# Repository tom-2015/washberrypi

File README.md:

# WashberryPi
The main controller board of our washing machine was broken so I decided to do something stupid: create a new controller board with a Raspberry Pi on it!
It turned out not so easy as thought, especially starting centrifuge without having unbalance making the machine to start walking proved a challenge.
After a few months testing and designing new PCB it was finally working again. It's not yet fully completed but if anyone else ever wants to do something this crazy I decided to put everything open source on github.

# Requirements
It's designed for a Samsung co bubble with DC motor but with some adjustments in software and PCB it will probably work with other machines that have a DC motor.
You'll need some skills for PCB design in Eagle, programming Raspberry Pi (Visual Basic .NET) and microcontrollers (Microchip PIC) in C.

# Contens
The repository contains 4 projects:
* Washmachine.sln: the main Visual Studio VB .NET project with software that runs on the Raspberry. This project is the main program of the washing machine. It controls all the components and provides a web interface.
* eagle directory: contains the Eagle files and Gerber files for the PCB that holds the Raspberry Pi Zero W, PIC microcontroller, relays and motor control components.
* pic directory: contains washing_machine.__c which is a Source Boost project containing C-code for the microcontroller that drives the TRIAC for motor.
* www directory: this is the web interface main directory.

# TIPS
Some tips if you want to make your washing machine Raspberry Pi controlled:
* be careful when applying power to the motor, I accidently applied power too fast resulting in a broken bearing! When testing the motor circuit add some resistors in series with the motor.
* If I need to redo the project I would consider using PWM with an IGBT or MOSFET to drive the motor and not using the original Samsung design with a TRIAC. This is because I think it's easier using PWM which in theory could be connected directly to the Pi instead of having a different microcontroller for it.
* Use a Raspberry Pi (2,3,4) with quad core instead of the single core Raspberry Pi Zero W. I needed to use an accelerometer to capture the drum vibrations and this required a thread to read 400 samples a second over I²C. This single core is often interrupted doing other stuff making the accelerometer buffer overflow.

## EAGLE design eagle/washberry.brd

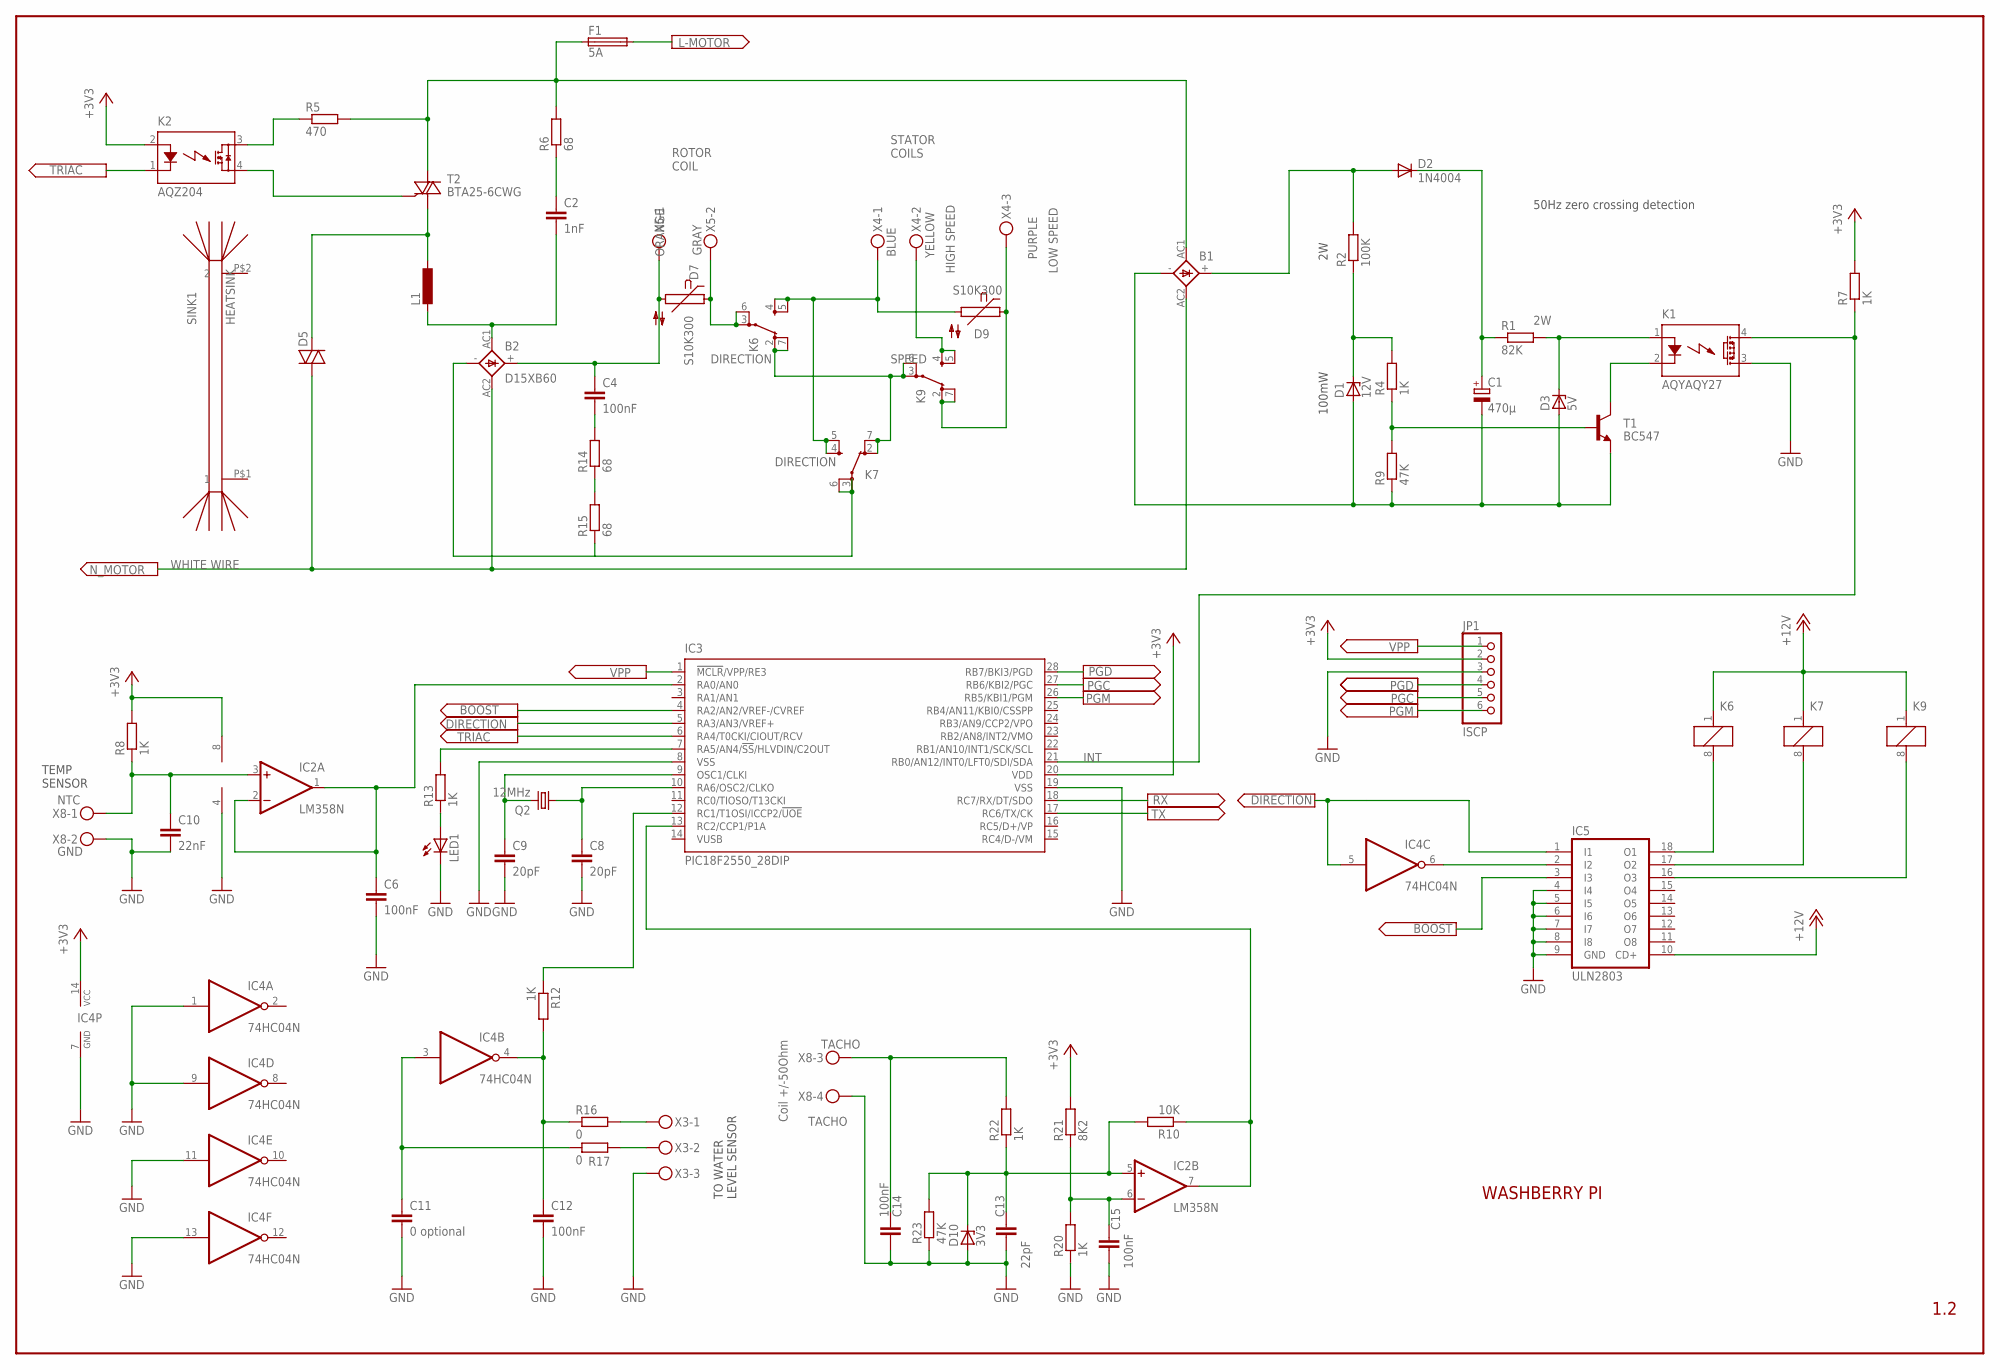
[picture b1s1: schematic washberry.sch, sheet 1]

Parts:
B1: 2KBB
B2: D15XB60; 5S
C1: 470µ; E5-13
C2: 1nF; C150-054X183
C4: 100nF; C150-054X183
C6, C12, C14, C15: 100nF; C025-024X044
C8, C9: 20pF; C025-024X044
C10: 22nF; C025-024X044
C11: 0 optional; C025-024X044
C13: 22pF; C025-024X044
D1: 12V; DO34Z7
D2: 1N4004; DO41-10
D3: 5V; DO34Z7
D5: DIAC-DO35-10; DO35-10
D7, D9: S10K300
D10: 3V3; DO34Z7
F1: 5A; GSH15
IC2: LM358N; DIL08
IC3: PIC18F2550_28DIP; DIL28-3
IC4: 74HC04N; DIL14
IC5: ULN2803; DIL18
JP1: ISCP; 1X06
K1: AQYAQY27; AQY27
K2: AQZ204; AQZ-SIL04
K6, K7, K9: FTR-K1C
L1: L-EUTJ5-U1; TJ5-U1
LED1: LEDCHIPLED_0805; CHIPLED_0805
Q2: 12MHz; HC49/S
R1: 82K; 0617/17
R2: 100K; 0617/17
R4, R7, R8, R12, R20, R22: 1K; 0411V
R5: 470; P0613/15
R6: 68; P0613/15
R9, R23: 47K; 0411V
R10: 10K; 0411V
R13: 1K; R0805
R14, R15: 68; 0617/17
R16, R17: 0; 0411V
R21: 8K2; 0411V
SINK1: HEATSINK; W_HEATSINK
T1: BC547; TO92
T2: BTA25-6CWG; TO220BV
X3, X4: MKDSN1,5/3-5,08
X5: MKDSN1,5/2-5,08
X8: MKDSN1,5/9-5,08

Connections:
+3V3: IC2.8 (V+), IC3.20 (VDD), IC4.14 (VCC), JP1.2, K2.2 (A), R7.2, R8.2, R21.2; also elsewhere on the board
+12V: IC5.10 (CD+), K6.1, K7.1, K9.1; also elsewhere on the board
BOOST: IC3.4 (RA2/AN2/VREF-/CVREF), IC5.3 (I3)
DIRECTION: IC3.5 (RA3/AN3/VREF+), IC4.5 (I), IC5.1 (I1)
GND: C6.2, C8.2, C9.2, C10.2, C11.2, C12.2, C13.2, C14.2, C15.2, D10.A, IC2.4 (V-), IC3.8 (VSS), IC3.19 (VSS), IC4.1 (I), IC4.7 (GND), IC4.9 (I), IC4.11 (I), IC4.13 (I), IC5.4 (I4), IC5.5 (I5), IC5.6 (I6), IC5.7 (I7), IC5.8 (I8), IC5.9 (GND), JP1.3, K1.3 (DS2), LED1.C, R20.1, R23.1, X3.3, X8.2, X8.4; also elsewhere on the board
INT: IC3.21 (RB0/AN12/INT0/LFT0/SDI/SDA), K1.4 (DS1), R7.1
L-MOTOR: F1.2; also elsewhere on the board
unnamed: K1.2 (K), T1.3 (C)
unnamed: B1.-, C1.-, D1.A, D3.A, R9.1, T1.1 (E)
unnamed: C1.+, D2.C, R1.1
unnamed: D3.C, K1.1 (A), R1.2
unnamed: IC3.7 (RA5/AN4/!SS!/HLVDIN/C2OUT), R13.2
unnamed: LED1.A, R13.1
unnamed: D1.C, R2.1, R4.2
unnamed: R4.1, R9.2, T1.2 (B)
unnamed: B1.+, D2.A, R2.2
unnamed: K2.4 (DS2), T2.G
unnamed: K2.3 (DS1), R5.1
unnamed: IC2.7 (OUT), IC3.13 (RC2/CCP1/P1A), R10.1
unnamed: B2.-, K7.3 (PA), K7.6 (PB), R15.1
unnamed: C2.1, R6.1
unnamed: B2.AC1, C2.2, L1.2
unnamed: C6.1, IC2.1 (OUT), IC2.2 (-IN), IC3.2 (RA0/AN0)
unnamed: K9.4 (SA), K9.5 (SB), X4.2
unnamed: D9.1, K9.2 (OA), K9.7 (OB), X4.3
unnamed: D5.C (2), L1.1, T2.T1 (A1)
unnamed: B2.+, C4.1, D7.2, X5.1
unnamed: C9.1, IC3.9 (OSC1/CLKI), Q2.2
unnamed: C8.1, IC3.10 (RA6/OSC2/CLKO), Q2.1
unnamed: IC3.12 (RC1/T1OSI/ICCP2/!UOE), R12.1
unnamed: C11.1, IC4.3 (I), R17.1
unnamed: C12.1, IC4.4 (O), R12.2, R16.1
unnamed: R14.1, R15.2
unnamed: C4.2, R14.2
unnamed: K6.2 (OA), K6.7 (OB), K7.2 (OA), K7.7 (OB), K9.3 (PA), K9.6 (PB)
unnamed: D9.2, K6.4 (SA), K6.5 (SB), K7.4 (SA), K7.5 (SB), X4.1
unnamed: D7.1, K6.3 (PA), K6.6 (PB), X5.2
unnamed: IC5.18 (O1), K6.8 (2)
unnamed: R16.2, X3.1
unnamed: R17.2, X3.2
unnamed: C15.1, IC2.6 (-IN), R20.2, R21.1
unnamed: C13.1, D10.C, IC2.5 (+IN), R10.2, R22.1, R23.2
unnamed: IC4.6 (O), IC5.2 (I2)
unnamed: IC5.17 (O2), K7.8 (2)
unnamed: IC5.16 (O3), K9.8 (2)
NTC: C10.1, IC2.3 (+IN), R8.1, X8.1
N_MOTOR: B1.AC2, B2.AC2, D5.A (1); also elsewhere on the board
PGC: IC3.27 (RB6/KBI2/PGC), JP1.5
PGD: IC3.28 (RB7/BKI3/PGD), JP1.4
PGM: IC3.26 (RB5/KBI1/PGM), JP1.6
RX: IC3.18 (RC7/RX/DT/SDO); also elsewhere on the board
SUPPLY_MOTOR: B1.AC1, F1.1, R5.2, R6.2, T2.T2 (A2)
TACHO: C14.1, R22.2, X8.3
TRIAC: IC3.6 (RA4/T0CKI/CIOUT/RCV), K2.1 (K)
TX: IC3.17 (RC6/TX/CK); also elsewhere on the board
VPP: IC3.1 (!MCLR!/VPP/RE3), JP1.1

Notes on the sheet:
100mW
TEMP SENSOR
WASHBERRY PI
1.2
ROTOR COIL
STATOR COILS
LOW SPEED
HIGH SPEED
DIRECTION
SPEED
50Hz zero crossing detection
WHITE WIRE
ORANGE
GRAY
BLUE
YELLOW
PURPLE
Coil +/-50Ohm
TO WATER LEVEL SENSOR

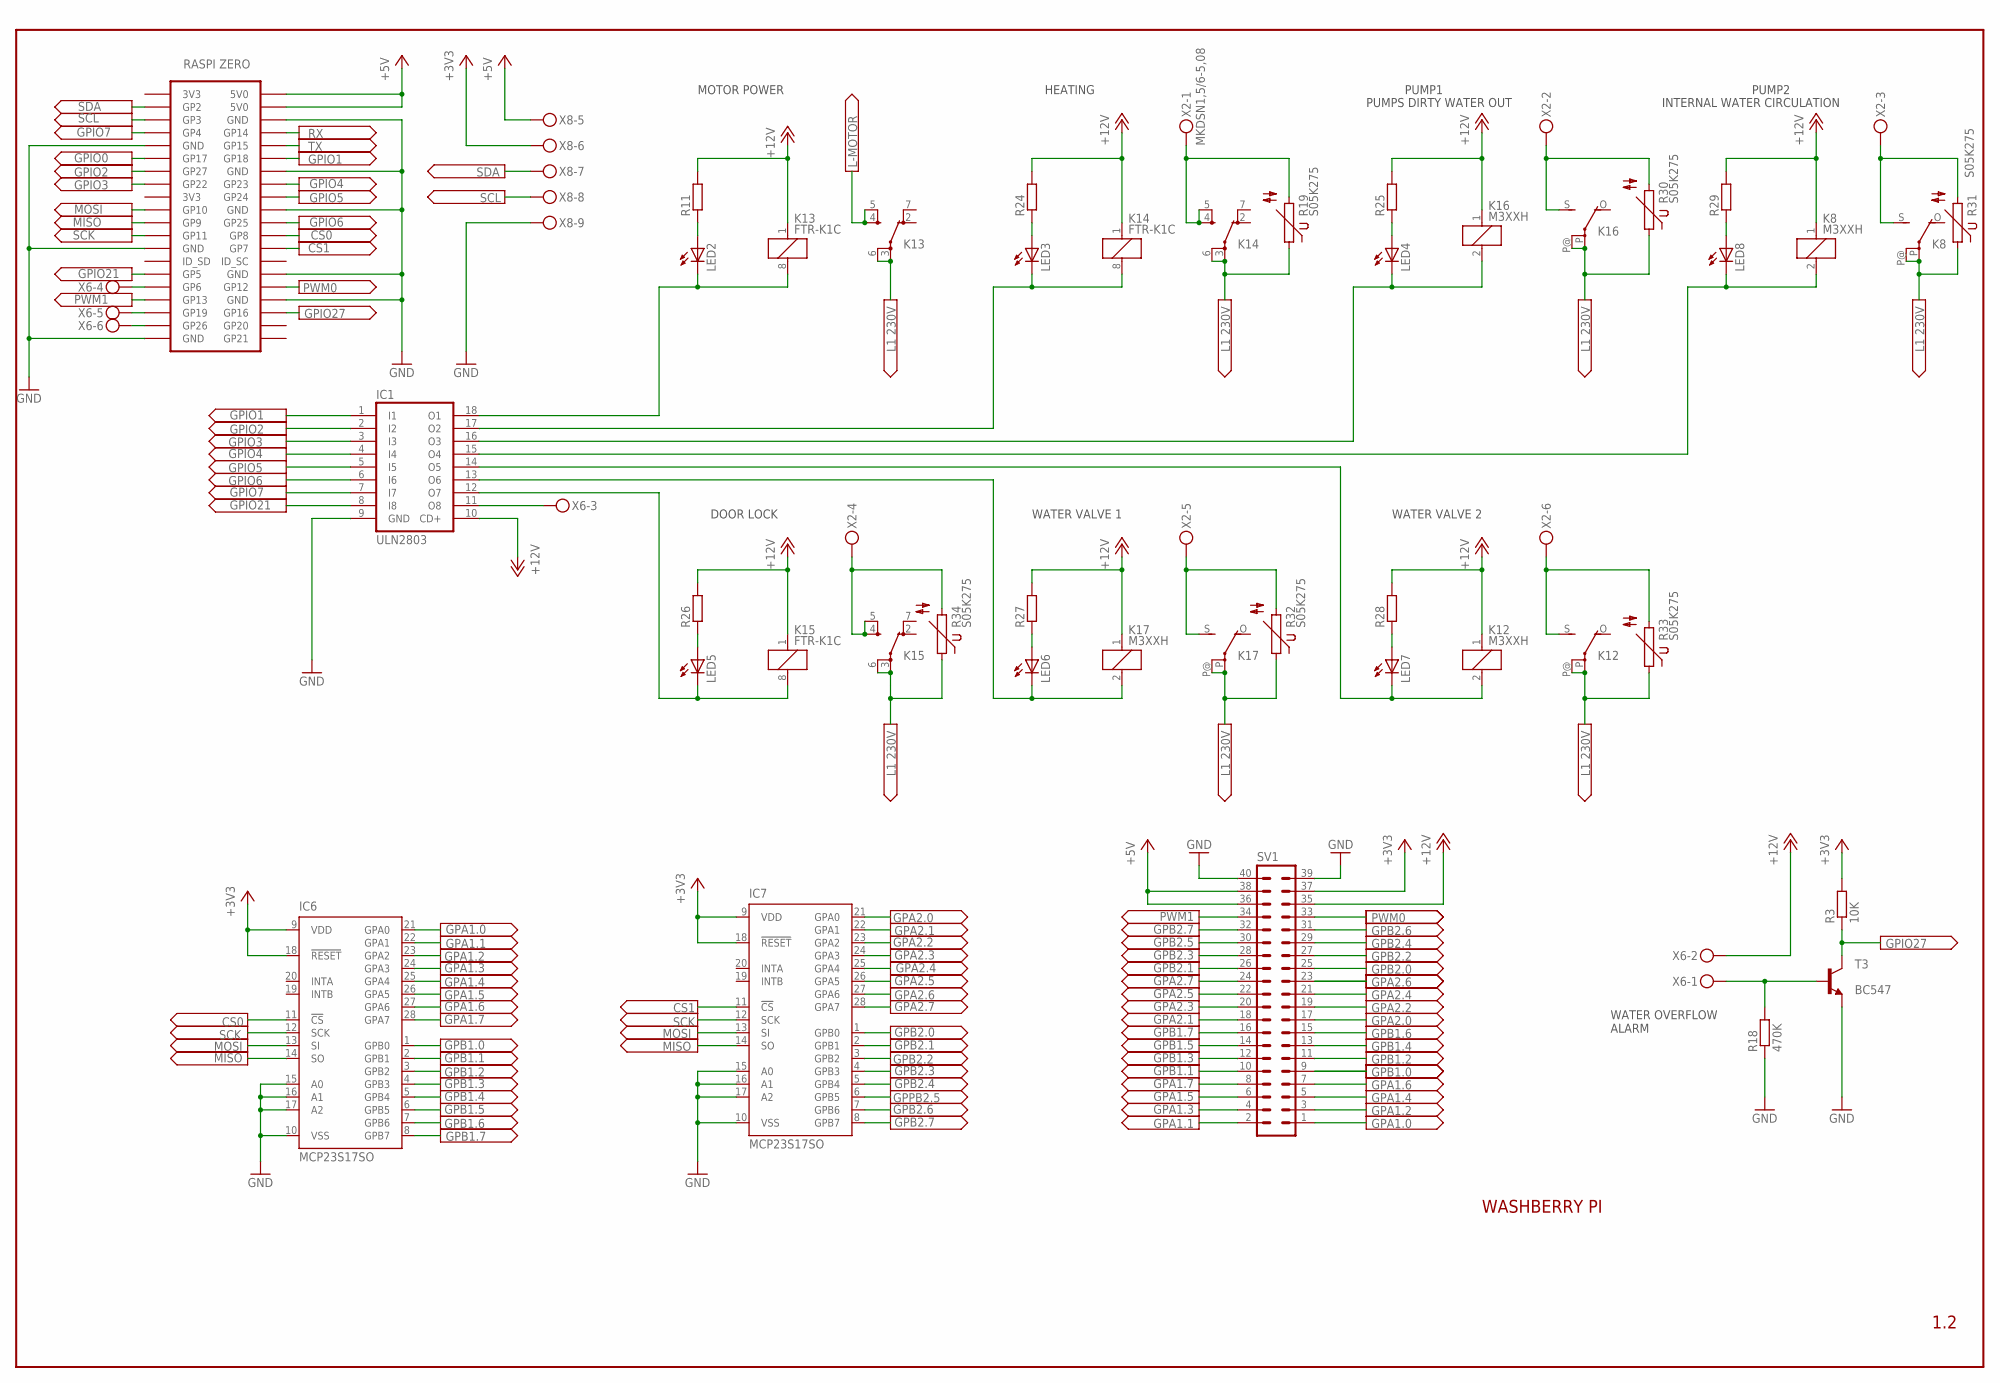
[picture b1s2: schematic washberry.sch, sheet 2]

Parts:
IC1: ULN2803; DIL18
IC6, IC7: MCP23S17SO; SO28W
K8, K12, K16, K17: M3XXH
K13, K14, K15: FTR-K1C
LED2, LED3, LED4, LED5, LED6, LED7, LED8: LEDSML0805; SML0805
R3: 10K; 0207/2V
R11, R24, R25, R26, R27, R28, R29: R-EU_R0805; R0805
R18: 470K; 0207/2V
R19, R30, R31, R32, R33, R34: S05K275
SV1: ML40
T3: BC547; TO92
U$3: ZERO; ZERO_NO_DIMENSION
X2, X6: MKDSN1,5/6-5,08
X8: MKDSN1,5/9-5,08

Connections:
+3V3: IC6.9 (VDD), IC6.18 (!RESET), IC7.9 (VDD), IC7.18 (!RESET), R3.2, SV1.37, X8.6; also elsewhere on the board
+5V: SV1.36, SV1.38, U$3.2 (5V0), U$3.4 (5V0), X8.5; also elsewhere on the board
+12V: IC1.10 (CD+), K8.1, K12.1, K13.1, K14.1, K15.1, K16.1, K17.1, R11.2, R24.2, R25.2, R26.2, R27.2, R28.2, R29.2, SV1.35, X6.2; also elsewhere on the board
CS0: IC6.11 (!CS), U$3.24 (GP8)
CS1: IC7.11 (!CS), U$3.26 (GP7)
GND: IC1.9 (GND), IC6.10 (VSS), IC6.15 (A0), IC6.16 (A1), IC6.17 (A2), IC7.10 (VSS), IC7.15 (A0), IC7.16 (A1), IC7.17 (A2), R18.1, SV1.39, SV1.40, T3.1 (E), U$3.6 (GND), U$3.9 (GND), U$3.14 (GND), U$3.20 (GND), U$3.25 (GND), U$3.30 (GND), U$3.34 (GND), U$3.39 (GND), X8.9; also elsewhere on the board
GPA1.0: IC6.21 (GPA0), SV1.1
GPA1.1: IC6.22 (GPA1), SV1.2
GPA1.2: IC6.23 (GPA2), SV1.3
GPA1.3: IC6.24 (GPA3), SV1.4
GPA1.4: IC6.25 (GPA4), SV1.5
GPA1.5: IC6.26 (GPA5), SV1.6
GPA1.6: IC6.27 (GPA6), SV1.7
GPA1.7: IC6.28 (GPA7), SV1.8
GPA2.0: IC7.21 (GPA0), SV1.17
GPA2.1: IC7.22 (GPA1), SV1.18
GPA2.2: IC7.23 (GPA2), SV1.19
GPA2.3: IC7.24 (GPA3), SV1.20
GPA2.4: IC7.25 (GPA4), SV1.21
GPA2.5: IC7.26 (GPA5), SV1.22
GPA2.6: IC7.27 (GPA6), SV1.23
GPA2.7: IC7.28 (GPA7), SV1.24
GPB1.0: IC6.1 (GPB0), SV1.9
GPB1.1: IC6.2 (GPB1), SV1.10
GPB1.2: IC6.3 (GPB2), SV1.11
GPB1.3: IC6.4 (GPB3), SV1.12
GPB1.4: IC6.5 (GPB4), SV1.13
GPB1.5: IC6.6 (GPB5), SV1.14
GPB1.6: IC6.7 (GPB6), SV1.15
GPB1.7: IC6.8 (GPB7), SV1.16
GPB2.0: IC7.1 (GPB0), SV1.25
GPB2.1: IC7.2 (GPB1), SV1.26
GPB2.2: IC7.3 (GPB2), SV1.27
GPB2.3: IC7.4 (GPB3), SV1.28
GPB2.4: IC7.5 (GPB4), SV1.29
GPB2.5: SV1.30
GPB2.6: IC7.7 (GPB6), SV1.31
GPB2.7: IC7.8 (GPB7), SV1.32
GPIO0: U$3.11 (GP17)
GPIO1: IC1.1 (I1), U$3.12 (GP18)
GPIO2: IC1.2 (I2), U$3.13 (GP27)
GPIO3: IC1.3 (I3), U$3.15 (GP22)
GPIO4: IC1.4 (I4), U$3.16 (GP23)
GPIO5: IC1.5 (I5), U$3.18 (GP24)
GPIO6: IC1.6 (I6), U$3.22 (GP25)
GPIO7: IC1.7 (I7), U$3.7 (GP4)
GPIO21: IC1.8 (I8), U$3.29 (GP5)
GPIO27: R3.1, T3.3 (C), U$3.36 (GP16)
GPPB2.5: IC7.6 (GPB5)
L: K8.P, K8.P@, K12.P, K12.P@, K13.3 (PA), K13.6 (PB), K14.3 (PA), K14.6 (PB), K15.3 (PA), K15.6 (PB), K16.P, K16.P@, K17.P, K17.P@, R19.1, R30.1, R31.1, R32.1, R33.1, R34.1; also elsewhere on the board
L-MOTOR: K13.4 (SA), K13.5 (SB); also elsewhere on the board
MISO: IC6.14 (SO), IC7.14 (SO), U$3.21 (GP9)
MOSI: IC6.13 (SI), IC7.13 (SI), U$3.19 (GP10)
unnamed: IC1.11 (O8), X6.3
unnamed: R18.2, T3.2 (B), X6.1
unnamed: IC1.18 (O1), K13.8 (2), LED2.C
unnamed: LED2.A, R11.1
unnamed: IC1.17 (O2), K14.8 (2), LED3.C
unnamed: LED3.A, R24.1
unnamed: IC1.16 (O3), K16.2, LED4.C
unnamed: U$3.31 (GP6), X6.4
unnamed: U$3.35 (GP19), X6.5
unnamed: LED4.A, R25.1
unnamed: LED5.A, R26.1
unnamed: IC1.13 (O6), K17.2, LED6.C
unnamed: LED6.A, R27.1
unnamed: IC1.14 (O5), K12.2, LED7.C
unnamed: LED7.A, R28.1
unnamed: IC1.15 (O4), K8.2, LED8.C
unnamed: LED8.A, R29.1
unnamed: IC1.12 (O7), K15.8 (2), LED5.C
unnamed: U$3.37 (GP26), X6.6
unnamed: K14.4 (SA), K14.5 (SB), R19.2, X2.1
unnamed: K16.S, R30.2, X2.2
unnamed: K8.S, R31.2, X2.3
unnamed: K12.S, R33.2, X2.6
unnamed: K17.S, R32.2, X2.5
unnamed: K15.4 (SA), K15.5 (SB), R34.2, X2.4
PWM0: SV1.33, U$3.32 (GP12)
PWM1: SV1.34, U$3.33 (GP13)
RX: U$3.8 (GP14); also elsewhere on the board
SCK: IC6.12 (SCK), IC7.12 (SCK), U$3.23 (GP11)
SCL: U$3.5 (GP3), X8.8
SDA: U$3.3 (GP2), X8.7
TX: U$3.10 (GP15); also elsewhere on the board

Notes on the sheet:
WASHBERRY PI
1.2
MOTOR POWER
HEATING
PUMP1
PUMP2
DOOR LOCK
WATER VALVE 1
WATER VALVE 2
PUMPS DIRTY WATER OUT
INTERNAL WATER CIRCULATION
WATER OVERFLOW ALARM

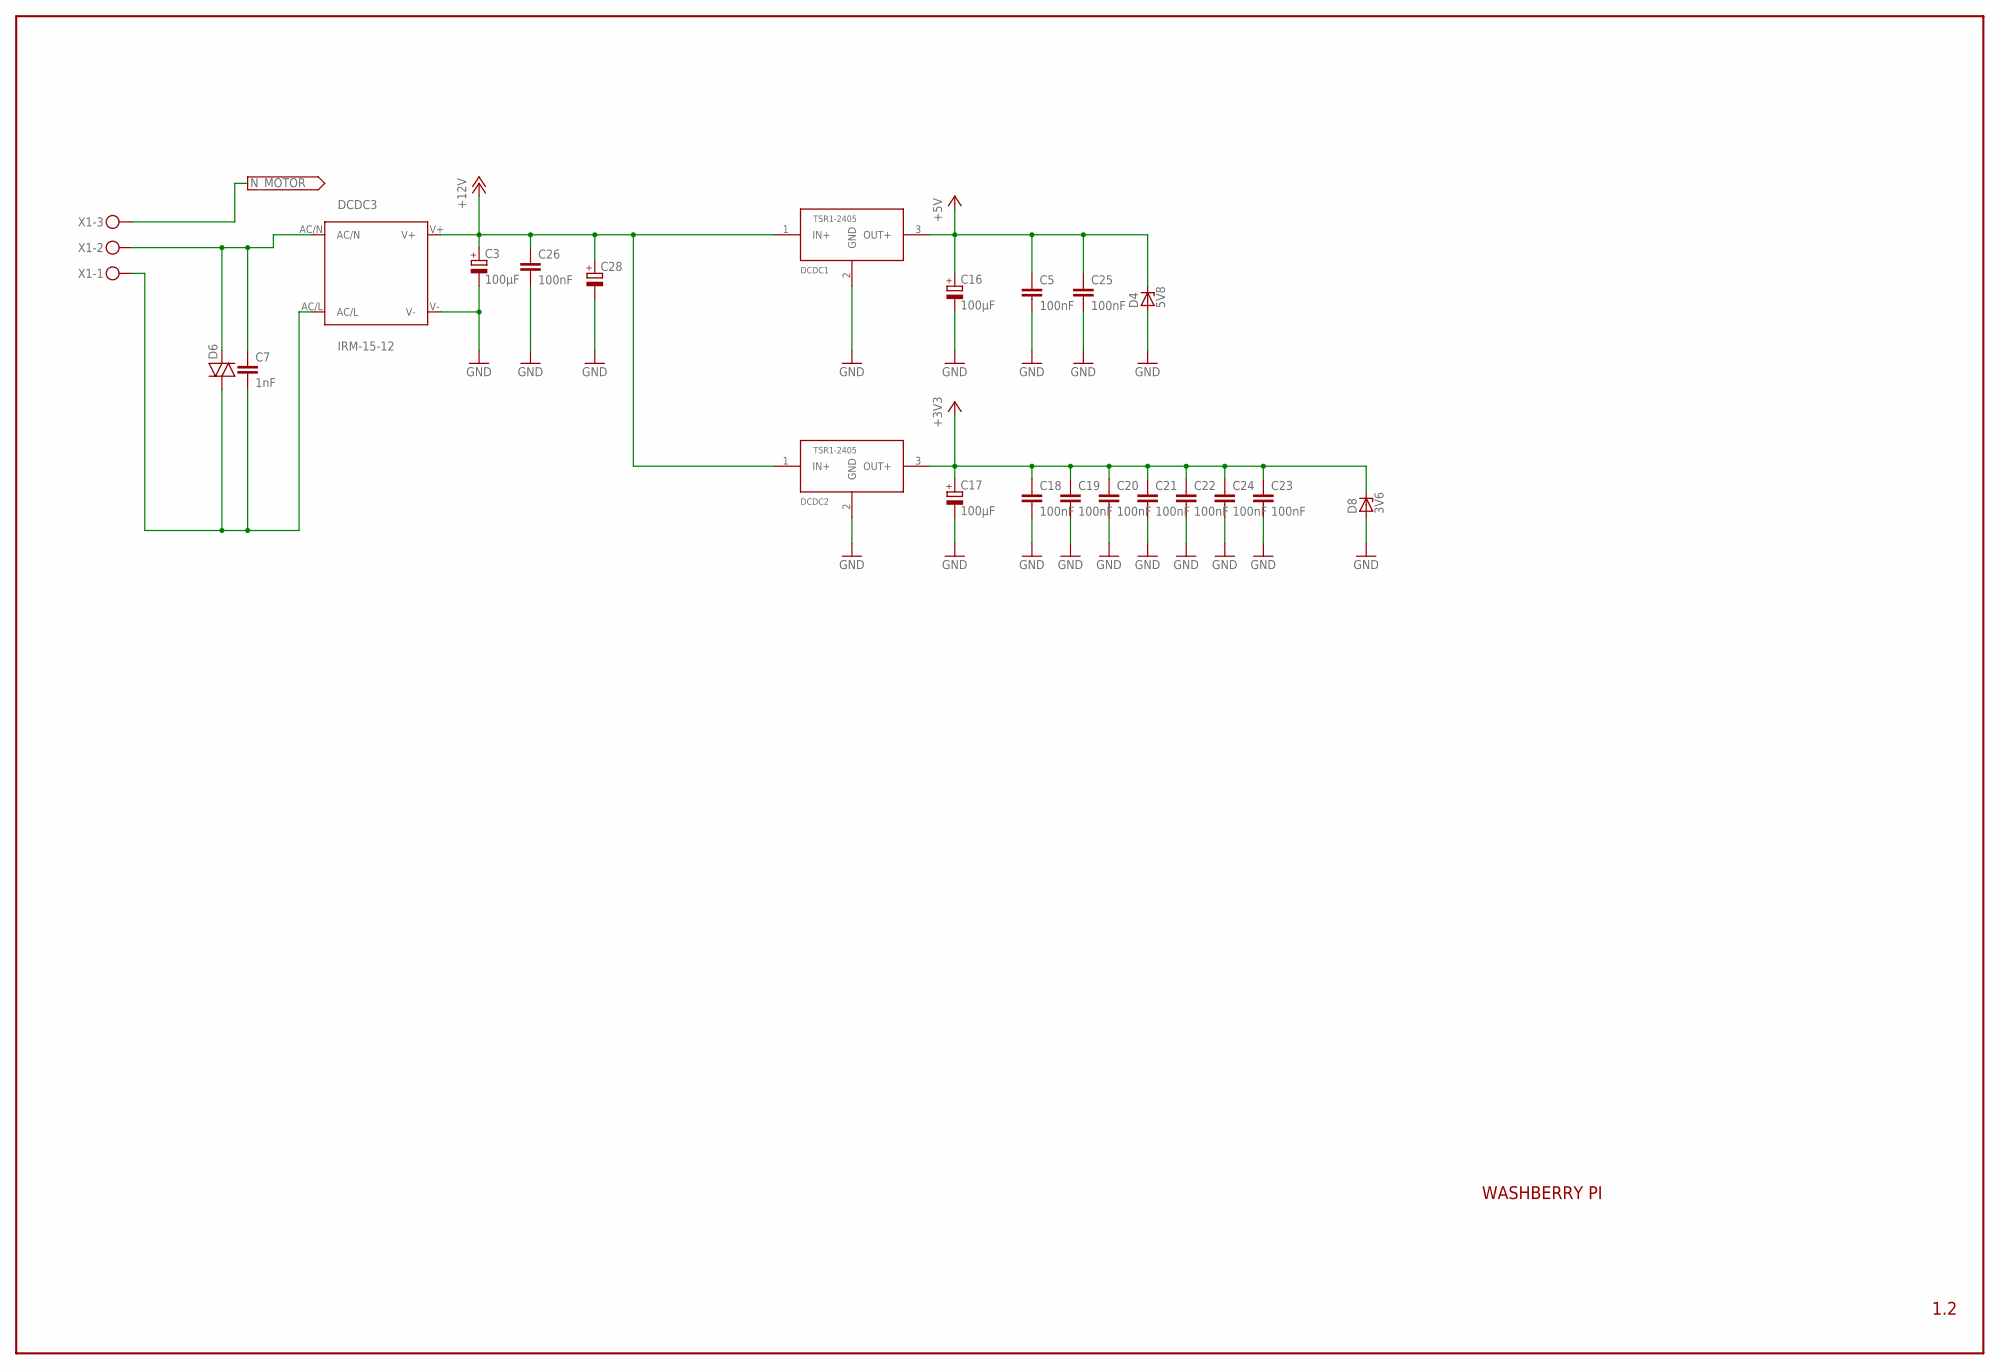
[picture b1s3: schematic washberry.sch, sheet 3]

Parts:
C3, C16: 100µF; E3,5-8
C5, C18, C19, C20, C21, C22, C23, C24, C25, C26: 100nF; C025-024X044
C7: 1nF; C150-091X182
C17: 100µF; E2-5
C28: CPOL-EUE2-5; E2-5
D4: 5V8; DO34Z7
D6: DIAC-DO35-10; DO35-10
D8: 3V6; DO34Z7
DCDC1, DCDC2: TSR1-2405; SIPTO220
DCDC3: IRM-15-12; IRM_15/20
X1: MKDSN1,5/3-5,08

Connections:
+3V3: C17.+, C18.1, C19.1, C20.1, C21.1, C22.1, C23.1, C24.1, D8.C, DCDC2.3 (OUT+); also elsewhere on the board
+5V: C5.1, C16.+, C25.1, D4.C, DCDC1.3 (OUT+); also elsewhere on the board
+12V: C3.+, C26.1, C28.+, DCDC1.1 (IN+), DCDC2.1 (IN+), DCDC3.V+; also elsewhere on the board
GND: C3.-, C5.2, C16.-, C17.-, C18.2, C19.2, C20.2, C21.2, C22.2, C23.2, C24.2, C25.2, C26.2, C28.-, D4.A, D8.A, DCDC1.2 (GND), DCDC2.2 (GND), DCDC3.V-; also elsewhere on the board
L: C7.2, D6.A (1), DCDC3.AC/L, X1.1; also elsewhere on the board
N: C7.1, D6.C (2), DCDC3.AC/N, X1.2
N_MOTOR: X1.3; also elsewhere on the board

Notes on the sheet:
WASHBERRY PI
1.2

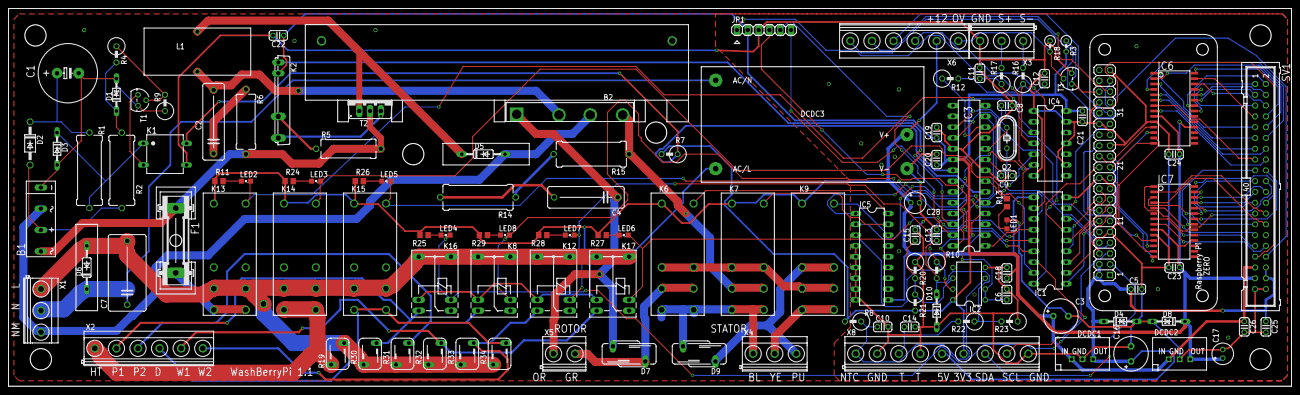
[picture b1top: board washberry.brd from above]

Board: 2 copper layers, 301.9 x 88.9 mm, 120 parts (0 on the bottom side), 133 nets.

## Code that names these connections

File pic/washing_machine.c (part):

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
int wanted_speed=0;
unsigned int current_speed=0;
bool direction=0;          //0 -> speed +, 1 -> speed -
bool changing_direction=0; //becomes 1 if we need to change direction (wait for 0 rpm)
bool speed_control_enabled=true;

unsigned int temperature=0; //holds result of ADC
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		set_power(0);
	}else if (rpm < 0){
		if (direction==0){
			direction=1;
			changing_direction=1;
			set_power(0);
		}
	}else{
		if (direction==1){
			direction=0;
			changing_direction=1;
			set_power(0);
		}
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	TRIAC_OUTPUT=TRIAC_OFF;
	cmcon=7; //disable comparator	
	trisa.0=1; //analog input
	trisa.2=0; //output boost
	trisa.3=0; //output direction
	trisa.4=0; //triac
	trisa.5=0; //LED
	trisa.1=0; //test
	trisb.0=1; //INT for zero crossing
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
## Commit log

2020-07-20 Start
2020-09-22 Fix bugs
    Fix bugs and some improvements, update to VS 2019
2020-09-22 Add BOM
    add BOM
2021-08-07 Improvements
    Improvements of constant values
    random washing delay
    add detection for temperature sensor problems, prevent overheating
